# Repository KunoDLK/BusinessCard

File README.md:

# BusinessCard
STM32 Based Business Card

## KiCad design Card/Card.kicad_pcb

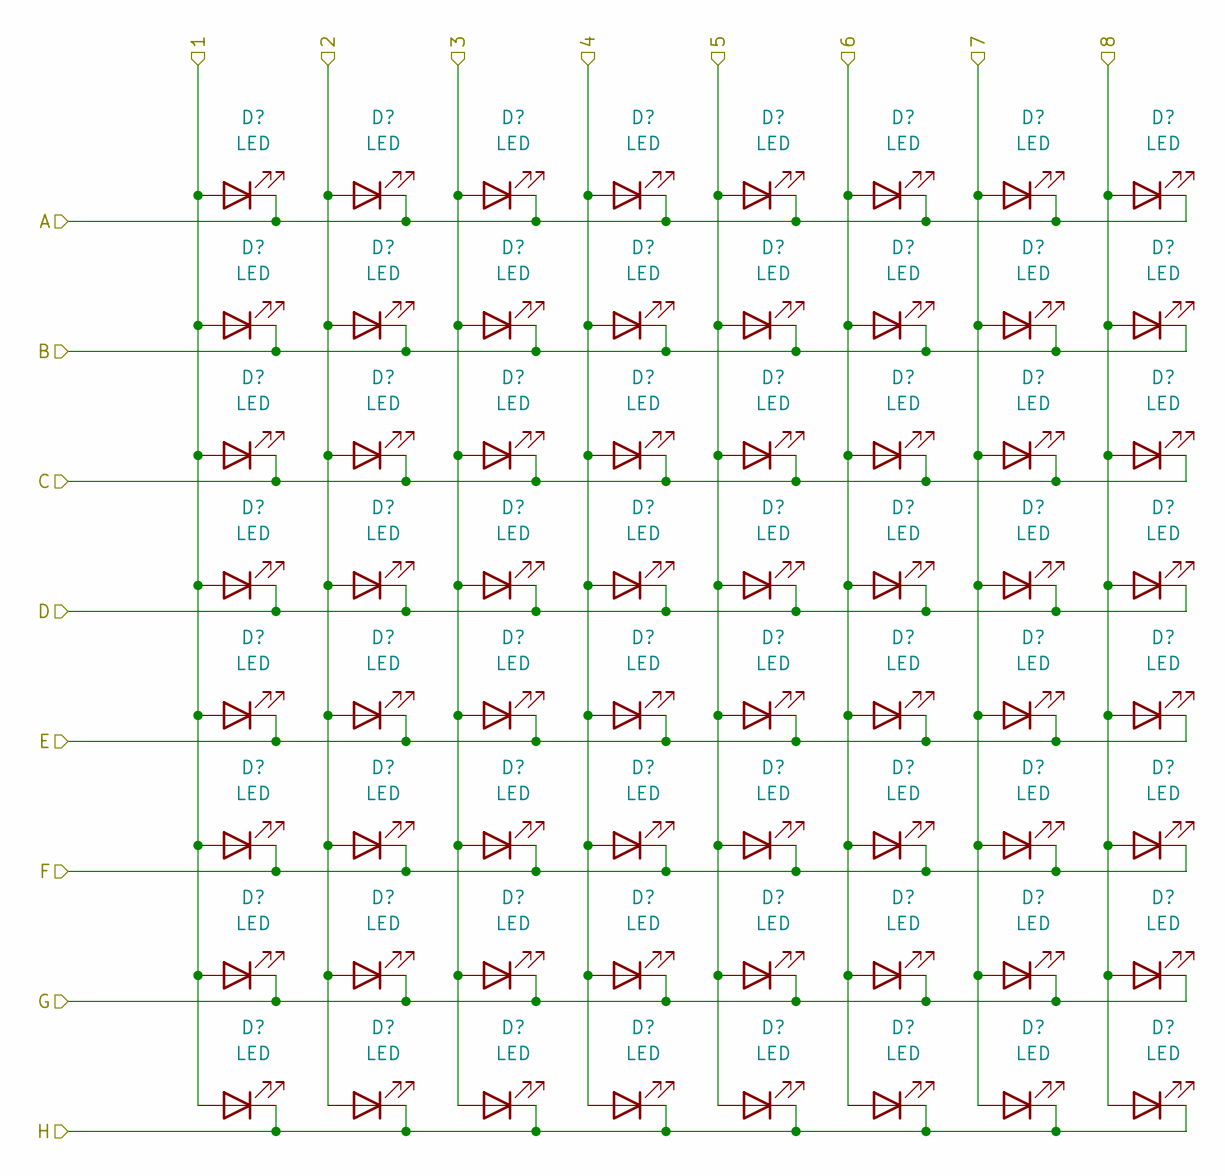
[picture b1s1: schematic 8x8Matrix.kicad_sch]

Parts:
D1, D2, D3, D4, D5, D6, D7, D8, D9, D10, D11, D12, D13, D14, D15, D16, D17, D18, D19, D20, D21, D22, D23, D24, D25, D26, D27, D28, D29, D30, D31, D32, D33, D34, D35, D36, D37, D38, D39, D40, D41, D42, D43, D44, D45, D46, D47, D48, D49, D50, D51, D52, D53, D54, D55, D56, D57, D58, D59, D60, D61, D62, D63, D64: LED; LED_0603_1608Metric

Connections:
/C0: D1.2 (A), D2.2 (A), D3.2 (A), D4.2 (A), D5.2 (A), D6.2 (A), D7.2 (A), D8.2 (A); also elsewhere on the board
/C1: D9.2 (A), D10.2 (A), D11.2 (A), D12.2 (A), D13.2 (A), D14.2 (A), D15.2 (A), D16.2 (A); also elsewhere on the board
/C2: D17.2 (A), D18.2 (A), D19.2 (A), D20.2 (A), D21.2 (A), D22.2 (A), D23.2 (A), D24.2 (A); also elsewhere on the board
/C3: D25.2 (A), D26.2 (A), D27.2 (A), D28.2 (A), D29.2 (A), D30.2 (A), D31.2 (A), D32.2 (A); also elsewhere on the board
/C4: D33.2 (A), D34.2 (A), D35.2 (A), D36.2 (A), D37.2 (A), D38.2 (A), D39.2 (A), D40.2 (A); also elsewhere on the board
/C5: D41.2 (A), D42.2 (A), D43.2 (A), D44.2 (A), D45.2 (A), D46.2 (A), D47.2 (A), D48.2 (A); also elsewhere on the board
/C6: D49.2 (A), D50.2 (A), D51.2 (A), D52.2 (A), D53.2 (A), D54.2 (A), D55.2 (A), D56.2 (A); also elsewhere on the board
/C7: D57.2 (A), D58.2 (A), D59.2 (A), D60.2 (A), D61.2 (A), D62.2 (A), D63.2 (A), D64.2 (A); also elsewhere on the board
/R0: D1.1 (K), D9.1 (K), D17.1 (K), D25.1 (K), D33.1 (K), D41.1 (K), D49.1 (K), D57.1 (K); also elsewhere on the board
/R1: D2.1 (K), D10.1 (K), D18.1 (K), D26.1 (K), D34.1 (K), D42.1 (K), D50.1 (K), D58.1 (K); also elsewhere on the board
/R2: D3.1 (K), D11.1 (K), D19.1 (K), D27.1 (K), D35.1 (K), D43.1 (K), D51.1 (K), D59.1 (K); also elsewhere on the board
/R3: D4.1 (K), D12.1 (K), D20.1 (K), D28.1 (K), D36.1 (K), D44.1 (K), D52.1 (K), D60.1 (K); also elsewhere on the board
/R4: D5.1 (K), D13.1 (K), D21.1 (K), D29.1 (K), D37.1 (K), D45.1 (K), D53.1 (K), D61.1 (K); also elsewhere on the board
/R5: D6.1 (K), D14.1 (K), D22.1 (K), D30.1 (K), D38.1 (K), D46.1 (K), D54.1 (K), D62.1 (K); also elsewhere on the board
/R6: D7.1 (K), D15.1 (K), D23.1 (K), D31.1 (K), D39.1 (K), D47.1 (K), D55.1 (K), D63.1 (K); also elsewhere on the board
/R7: D8.1 (K), D16.1 (K), D24.1 (K), D32.1 (K), D40.1 (K), D48.1 (K), D56.1 (K), D64.1 (K); also elsewhere on the board

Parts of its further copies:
D65, D66, D67, D68, D69, D70, D71, D72, D73, D74, D75, D76, D77, D78, D79, D80, D81, D82, D83, D84, D85, D86, D87, D88, D89, D90, D91, D92, D93, D94, D95, D96, D97, D98, D99, D100, D101, D102, D103, D104, D105, D106, D107, D108, D109, D110, D111, D112, D113, D114, D115, D116, D117, D118, D119, D120, D121, D122, D123, D124, D125, D126, D127, D128, D129, D130, D131, D132, D133, D134, D135, D136, D137, D138, D139, D140, D141, D142, D143, D144, D145, D146, D147, D148, D149, D150, D151, D152, D153, D154, D155, D156, D157, D158, D159, D160, D161, D162, D163, D164, D165, D166, D167, D168, D169, D170, D171, D172, D173, D174, D175, D176, D177, D178, D179, D180, D181, D182, D183, D184, D185, D186, D187, D188, D189, D190, D191, D192, D193, D194, D195, D196, D197, D198, D199, D200, D201, D202, D203, D204, D205, D206, D207, D208, D209, D210, D211, D212, D213, D214, D215, D216, D217, D218, D219, D220, D221, D222, D223, D224, D225, D226, D227, D228, D229, D230, D231, D232, D233, D234, D235, D236, D237, D238, D239, D240, D241, D242, D243, D244, D245, D246, D247, D248, D249, D250, D251, D252, D253, D254, D255, D256: LED; LED_0603_1608Metric

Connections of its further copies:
/C0: D129.2 (A), D130.2 (A), D131.2 (A), D132.2 (A), D133.2 (A), D134.2 (A), D135.2 (A), D136.2 (A); also elsewhere on the board
/C1: D137.2 (A), D138.2 (A), D139.2 (A), D140.2 (A), D141.2 (A), D142.2 (A), D143.2 (A), D144.2 (A); also elsewhere on the board
/C2: D145.2 (A), D146.2 (A), D147.2 (A), D148.2 (A), D149.2 (A), D150.2 (A), D151.2 (A), D152.2 (A); also elsewhere on the board
/C3: D153.2 (A), D154.2 (A), D155.2 (A), D156.2 (A), D157.2 (A), D158.2 (A), D159.2 (A), D160.2 (A); also elsewhere on the board
/C4: D161.2 (A), D162.2 (A), D163.2 (A), D164.2 (A), D165.2 (A), D166.2 (A), D167.2 (A), D168.2 (A); also elsewhere on the board
/C5: D169.2 (A), D170.2 (A), D171.2 (A), D172.2 (A), D173.2 (A), D174.2 (A), D175.2 (A), D176.2 (A); also elsewhere on the board
/C6: D177.2 (A), D178.2 (A), D179.2 (A), D180.2 (A), D181.2 (A), D182.2 (A), D183.2 (A), D184.2 (A); also elsewhere on the board
/C7: D185.2 (A), D186.2 (A), D187.2 (A), D188.2 (A), D189.2 (A), D190.2 (A), D191.2 (A), D192.2 (A); also elsewhere on the board
/C8: D65.2 (A), D66.2 (A), D67.2 (A), D68.2 (A), D69.2 (A), D70.2 (A), D71.2 (A), D72.2 (A), D193.2 (A), D194.2 (A), D195.2 (A), D196.2 (A), D197.2 (A), D198.2 (A), D199.2 (A), D200.2 (A)
/C9: D73.2 (A), D74.2 (A), D75.2 (A), D76.2 (A), D77.2 (A), D78.2 (A), D79.2 (A), D80.2 (A), D201.2 (A), D202.2 (A), D203.2 (A), D204.2 (A), D205.2 (A), D206.2 (A), D207.2 (A), D208.2 (A)
/C10: D81.2 (A), D82.2 (A), D83.2 (A), D84.2 (A), D85.2 (A), D86.2 (A), D87.2 (A), D88.2 (A), D209.2 (A), D210.2 (A), D211.2 (A), D212.2 (A), D213.2 (A), D214.2 (A), D215.2 (A), D216.2 (A)
/C11: D89.2 (A), D90.2 (A), D91.2 (A), D92.2 (A), D93.2 (A), D94.2 (A), D95.2 (A), D96.2 (A), D217.2 (A), D218.2 (A), D219.2 (A), D220.2 (A), D221.2 (A), D222.2 (A), D223.2 (A), D224.2 (A)
/C12: D97.2 (A), D98.2 (A), D99.2 (A), D100.2 (A), D101.2 (A), D102.2 (A), D103.2 (A), D104.2 (A), D225.2 (A), D226.2 (A), D227.2 (A), D228.2 (A), D229.2 (A), D230.2 (A), D231.2 (A), D232.2 (A)
/C13: D105.2 (A), D106.2 (A), D107.2 (A), D108.2 (A), D109.2 (A), D110.2 (A), D111.2 (A), D112.2 (A), D233.2 (A), D234.2 (A), D235.2 (A), D236.2 (A), D237.2 (A), D238.2 (A), D239.2 (A), D240.2 (A)
/C14: D113.2 (A), D114.2 (A), D115.2 (A), D116.2 (A), D117.2 (A), D118.2 (A), D119.2 (A), D120.2 (A), D241.2 (A), D242.2 (A), D243.2 (A), D244.2 (A), D245.2 (A), D246.2 (A), D247.2 (A), D248.2 (A)
/C15: D121.2 (A), D122.2 (A), D123.2 (A), D124.2 (A), D125.2 (A), D126.2 (A), D127.2 (A), D128.2 (A), D249.2 (A), D250.2 (A), D251.2 (A), D252.2 (A), D253.2 (A), D254.2 (A), D255.2 (A), D256.2 (A)
/R0: D65.1 (K), D73.1 (K), D81.1 (K), D89.1 (K), D97.1 (K), D105.1 (K), D113.1 (K), D121.1 (K); also elsewhere on the board
/R1: D66.1 (K), D74.1 (K), D82.1 (K), D90.1 (K), D98.1 (K), D106.1 (K), D114.1 (K), D122.1 (K); also elsewhere on the board
/R2: D67.1 (K), D75.1 (K), D83.1 (K), D91.1 (K), D99.1 (K), D107.1 (K), D115.1 (K), D123.1 (K); also elsewhere on the board
/R3: D68.1 (K), D76.1 (K), D84.1 (K), D92.1 (K), D100.1 (K), D108.1 (K), D116.1 (K), D124.1 (K); also elsewhere on the board
/R4: D69.1 (K), D77.1 (K), D85.1 (K), D93.1 (K), D101.1 (K), D109.1 (K), D117.1 (K), D125.1 (K); also elsewhere on the board
/R5: D70.1 (K), D78.1 (K), D86.1 (K), D94.1 (K), D102.1 (K), D110.1 (K), D118.1 (K), D126.1 (K); also elsewhere on the board
/R6: D71.1 (K), D79.1 (K), D87.1 (K), D95.1 (K), D103.1 (K), D111.1 (K), D119.1 (K), D127.1 (K); also elsewhere on the board
/R7: D72.1 (K), D80.1 (K), D88.1 (K), D96.1 (K), D104.1 (K), D112.1 (K), D120.1 (K), D128.1 (K); also elsewhere on the board
/R8: D129.1 (K), D137.1 (K), D145.1 (K), D153.1 (K), D161.1 (K), D169.1 (K), D177.1 (K), D185.1 (K), D193.1 (K), D201.1 (K), D209.1 (K), D217.1 (K), D225.1 (K), D233.1 (K), D241.1 (K), D249.1 (K)
/R9: D130.1 (K), D138.1 (K), D146.1 (K), D154.1 (K), D162.1 (K), D170.1 (K), D178.1 (K), D186.1 (K), D194.1 (K), D202.1 (K), D210.1 (K), D218.1 (K), D226.1 (K), D234.1 (K), D242.1 (K), D250.1 (K)
/R10: D131.1 (K), D139.1 (K), D147.1 (K), D155.1 (K), D163.1 (K), D171.1 (K), D179.1 (K), D187.1 (K), D195.1 (K), D203.1 (K), D211.1 (K), D219.1 (K), D227.1 (K), D235.1 (K), D243.1 (K), D251.1 (K)
/R11: D132.1 (K), D140.1 (K), D148.1 (K), D156.1 (K), D164.1 (K), D172.1 (K), D180.1 (K), D188.1 (K), D196.1 (K), D204.1 (K), D212.1 (K), D220.1 (K), D228.1 (K), D236.1 (K), D244.1 (K), D252.1 (K)
/R12: D133.1 (K), D141.1 (K), D149.1 (K), D157.1 (K), D165.1 (K), D173.1 (K), D181.1 (K), D189.1 (K), D197.1 (K), D205.1 (K), D213.1 (K), D221.1 (K), D229.1 (K), D237.1 (K), D245.1 (K), D253.1 (K)
/R13: D134.1 (K), D142.1 (K), D150.1 (K), D158.1 (K), D166.1 (K), D174.1 (K), D182.1 (K), D190.1 (K), D198.1 (K), D206.1 (K), D214.1 (K), D222.1 (K), D230.1 (K), D238.1 (K), D246.1 (K), D254.1 (K)
/R14: D135.1 (K), D143.1 (K), D151.1 (K), D159.1 (K), D167.1 (K), D175.1 (K), D183.1 (K), D191.1 (K), D199.1 (K), D207.1 (K), D215.1 (K), D223.1 (K), D231.1 (K), D239.1 (K), D247.1 (K), D255.1 (K)
/R15: D136.1 (K), D144.1 (K), D152.1 (K), D160.1 (K), D168.1 (K), D176.1 (K), D184.1 (K), D192.1 (K), D200.1 (K), D208.1 (K), D216.1 (K), D224.1 (K), D232.1 (K), D240.1 (K), D248.1 (K), D256.1 (K)

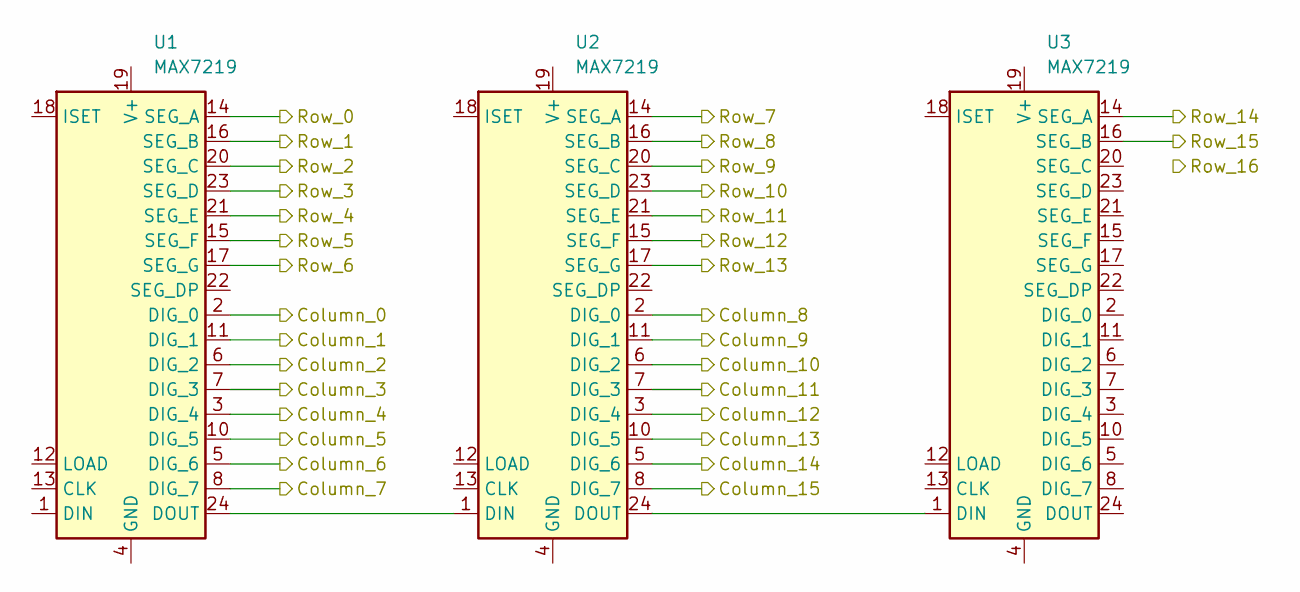
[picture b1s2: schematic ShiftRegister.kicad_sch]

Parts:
U1, U2, U3: MAX7219

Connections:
unnamed: U1.4 (GND), U1.9 (GND)
unnamed: U1.24 (DOUT), U2.1 (DIN)
unnamed: U2.4 (GND), U2.9 (GND)
unnamed: U2.24 (DOUT), U3.1 (DIN)
unnamed: U3.4 (GND), U3.9 (GND)

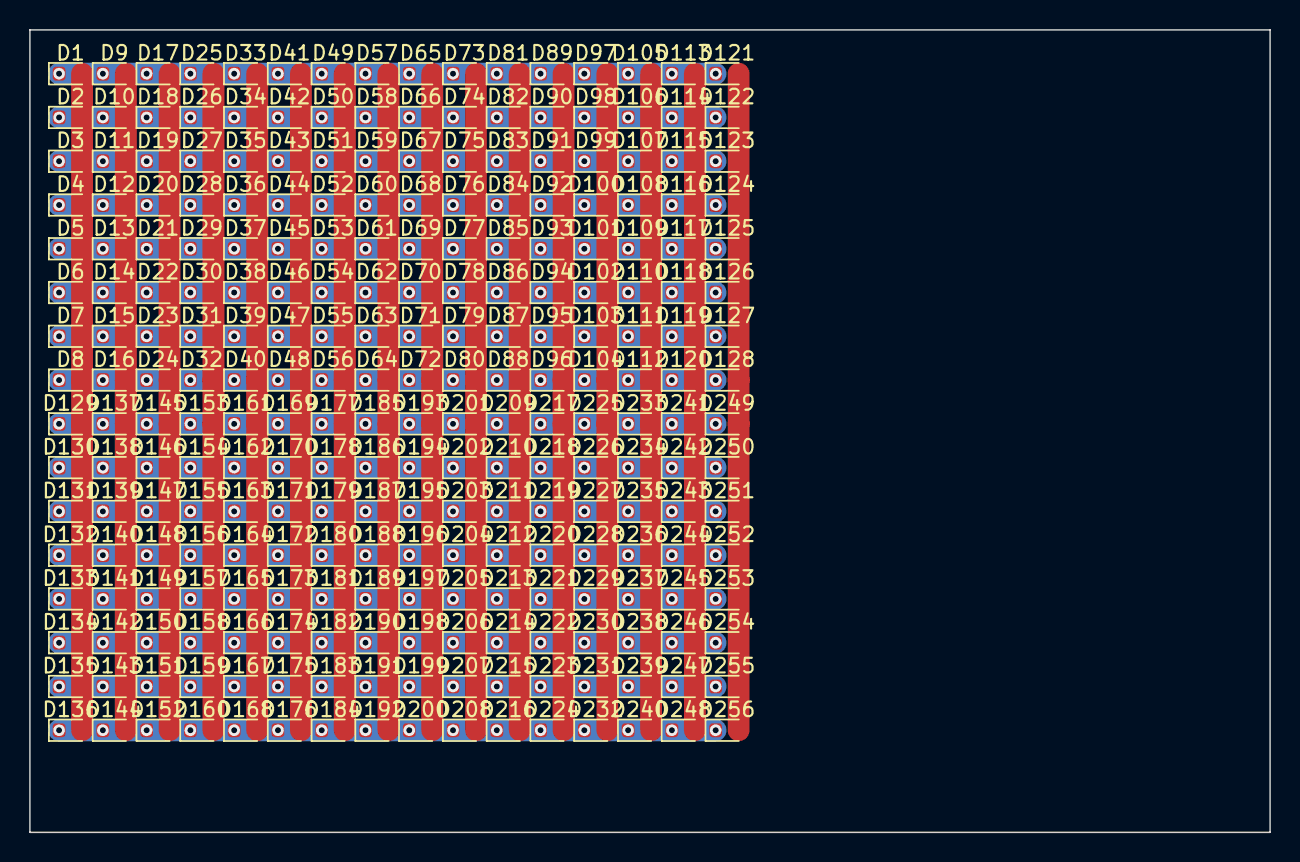
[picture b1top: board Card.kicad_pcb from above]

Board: 2 copper layers, 85.0 x 55.0 mm, 256 parts (0 on the bottom side), 32 nets.

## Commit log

2025-02-02 changed to 3.5mm LEDs
2025-02-02 Updated to UK card size
2025-02-02 created LED matrix
